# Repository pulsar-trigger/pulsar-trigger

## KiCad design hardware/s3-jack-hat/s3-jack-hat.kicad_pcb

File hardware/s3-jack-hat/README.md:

<!--
SPDX-License-Identifier: GPL-3.0-or-later
Copyright (C) 2026 Pulsar Trigger contributors
-->

# S3 Jack Hat (KiCad 10)

Source: written for Pulsar.

**Status: r0.1 built (JLC, 2026-11) and its header is mirrored end to end - it does not
work as shipped. Rework below; r0.2 = regenerate from the fixed
[tools/hat2.py](tools/hat2.py) with `tools/build.sh` before ordering again.** The files in
`out/` and the `.kicad_pcb` are still r0.1. The PJ-242 pin roles are read from the
maker's drawing, not yet measured.

## 🔴 r0.1: header mirrored end to end (found 2026-11-24)

Plugged in with its components towards the stick's back (the only way the case takes it),
r0.1's square pad 1 sits at the **G3 / 5V_IN** end of the socket, not the G5 / GND end:

| r0.1 net | Pad | Meant for | Lands on (normal) | Lands on (upside down) |
| --- | --- | --- | --- | --- |
| Shutter (R1, U1) | 1 | G5 | G3 | the stick's GND (can never fire) |
| Board GND | 2 | GND | **5V_IN** | G5 |
| Focus (R3, U2) | 5 | G6 | G44 (UART TX) | **G0** (boot strap) |

So nothing fires the normal way. Upside down, focus follows G5 and G0, and G0 is tied to
the focus net, which can boot the stick into download mode. Use it neither way unrepaired.

**Rework (three wires, three pins):**

1. Clip or pull the header pins of **pads 1, 2 and 5** so they no longer enter the socket.
   Pad 2 is the one that matters: left in, it shorts 5V_IN to ground once step 2 is done.
2. Wire, on the board: **pad 1 → pad 15** (lands on G5), **pad 2 → pad 16** (GND),
   **pad 5 → pad 11** (G6). Pads 11, 15 and 16 are unconnected on r0.1.
3. Before power, plugged in normally: board GND to the stick's USB-C shell **beeps**;
   board GND to 5V_IN does **not**; the jack sleeve to board GND stays **open**.
4. Dry run with a plug: focus closes ring-sleeve, shutter closes tip-sleeve.

**Cause:** `GND_CORNER`'s side. The row was right, the end was not; the stick's label
reading below still holds for which row, and `("lower", "right")` is what the footprint
needs. With that value `hat2.py` maps G5 → pad 15, GND → pad 16, G6 → pad 11 - exactly
where the rework puts them.

This is a small board that plugs into the M5StickS3's Hat2-Bus and drives a Canon 2.5 mm
remote jack:

- G5 drives the shutter and G6 drives focus.
- Each line goes through an LTV-817S optocoupler, so the camera stays isolated from the
  stick.
- The board has no battery, charger, USB or boost converter. The stick runs on its own
  battery, or on a power bank plugged into its USB-C.

The larger hat (USB host bridge and LiPo power) is parked. It is in
[docs/hardware-s3-hat.md](../../docs/hardware-s3-hat.md) and [../s3-hat/](../s3-hat/).

```mermaid
flowchart LR
    G5["Hat2 G5"] --> R1["R1 330R"] --> U1["U1 LTV-817S<br/>shutter"]
    G6["Hat2 G6"] --> R3["R3 330R"] --> U2["U2 LTV-817S<br/>focus"]
    G5 --> R2["R2 100k to GND"]
    G6 --> R4["R4 100k to GND"]
    U1 -- "collector" --> TIP["J2 tip (pin 6)"]
    U2 -- "collector" --> RING["J2 ring (pin 4)"]
    U1 -- "emitter" --> SLV["J2 sleeve (pins 2+3)<br/>camera ground, not board GND"]
    U2 -- "emitter" --> SLV
```

## 🔴 Unverified before ordering

1. ~~**Header orientation.**~~ **Settled 2026-11-10, WRONG END - fixed 2026-11-24 to
   `("lower", "right")`, see "r0.1: header mirrored" above.** It read: `GND_CORNER = ("lower", "left")`
   in [tools/hat2.py](tools/hat2.py). GND is in the row nearer the stick's back, at the
   LED end of the socket. Four sources agree: the stick's back sticker, whose label lines
   are laid out like the rows, and Bruce firmware's CC1101, SD card and NRF24 wiring
   diagrams for the StickS3. The first guess, `("upper", "left")`, was wrong: it would
   have swapped every pin pair and put the focus line on G0, the boot strap pin.
2. **PJ-242 pin roles.** The pins were read from the maker's drawing: 6 = tip, 4 = ring,
   2 + 3 = sleeve, 5/7 = switch contacts. See "PJ-242 pin roles" in the parked spec.
   Check them with a meter and a Canon plug.

## Hat2-Bus pin map (source checked)

Two sources give the same map:

- **M5Stack's StickS3 docs PDF, page 10, "Hat2-Bus".** It lists the LEFT column as pins 1, 3, … 15 and the
  RIGHT column as pins 2, 4, … 16.
- **The stick's schematic, page 4 (the BTB small board, CN2, "2×8 female, plastic height
  8.5, P = 2.54").** It numbers the same socket the other way: pins 1–8 down one row and
  16–9 back up the other. The pairs across the socket (GND/G5, EXT_5V/G4, BOOT/G6, G1/G7,
  G8/G43, BAT/G44, 3V3/G2, 5V_IN/G3) are identical, so the two numberings describe the
  same socket.

This board uses M5's odd/even numbers.

| Column | 1 | 2 | 3 | 4 | 5 | 6 | 7 | 8 |
| --- | --- | --- | --- | --- | --- | --- | --- | --- |
| Odd pin (1–15) | GND | EXT_5V | G0 (Boot) | G1 | G8 | BAT | 3V3_L2 | 5V_IN |
| Even pin (2–16) | G5 | G4 | G6 | G7 | G43 | G44 | G2 | G3 |

**G5 and G6 are free.** In the stick's schematic, EXT_GPIO5/6 run only from the ESP32-S3
(GPIO5/GPIO6, pins 10/11) through the board-to-board connectors to the Hat socket. They
have no other load, pull or function. G0 and G3 are boot-strapping pins and are left
unconnected. Every pin except GND, G5 and G6 carries a no-connect flag.

## Files

| Path | What |
| --- | --- |
| `s3-jack-hat.kicad_pro`, `.kicad_sch`, `.kicad_pcb` | The project. The board is saved with its zones filled |
| `s3-jack-hat.kicad_dru` | Custom rule: the camera side (jack nets) keeps ≥ 1 mm from everything else |
| `s3-jack-hat.kicad_sym`, `s3-jack-hat.pretty/` | The PJ-242 symbol and footprint (generated) |
| `tools/hat2.py` | **The one orientation choice** (`GND_CORNER`) and the Hat2 map |
| `tools/gen_schematic.py` | Writes the schematic. Its symbol engine is copied from `../s3-hat/tools/` |
| `tools/gen_pcb.py` | Writes the PJ-242 footprint and the board from the exported netlist |
| `tools/check_netlist.py` | Asserts every required connection, and every unconnected pin |
| `tools/jlc_files.py` | Writes the JLC BOM and CPL |
| `tools/build.sh` | Runs everything above, then exports the fabrication files |
| `out/` | ERC/DRC reports, netlist, Gerbers + drill (folder and zip), BOM, CPL, schematic PDF, renders |

**Edit the scripts, not the KiCad files.** The next build overwrites any hand edit.

## Regenerate and check

```sh
hardware/s3-jack-hat/tools/build.sh     # exit 0 = everything below passed
```

The script stops at the first failure. It runs:

1. the footprint;
2. the schematic;
3. ERC (`--exit-code-violations`, so any warning fails too);
4. the netlist export and `check_netlist.py`;
5. the board;
6. DRC with zone refill and schematic parity. It fails on any error, or on any warning
   other than the one expected below;
7. the Gerbers, drill files, position file, JLC CSVs, schematic PDF and renders.

**Results on 2026-11-10:**

- **ERC:** 0 violations.
- **Netlist check:** all 48 checks pass (exit 0). Verified that it can fail: a netlist
  with the sleeve merged into GND fails it (exit 1).
- **DRC:** 0 errors, 0 unconnected, 0 schematic-parity issues, and 1 warning. The warning
  is `lib_footprint_mismatch` on J1, because the generator drops the header's silkscreen
  where it would hang over the board edge.
- **The isolation rule fires.** A test GND via placed 0.6 mm from the tip pad was flagged:
  "rule 'camera side isolation' clearance 1.0000 mm; actual 0.6000 mm". The default
  0.2 mm rule would have passed it.

The 3D renders show only the bare board. This KiCad install has no 3D models, so no part
bodies are drawn.

## BOM (JLC parts checked 2026-11-10 through JLC's parts API)

| Ref | Part | LCSC | JLC type | Stock 11-10 | Notes |
| --- | --- | --- | --- | --- | --- |
| J1 | Hong Cheng HC-PZ254-13.8L-2x8PWA, 2×8 right-angle male, 2.54 mm | C27985210 | Extended | 1381 | Through-hole: needs JLC's THT assembly, or hand soldering. It was chosen over C54907672 because it has a drawing (2.5 mm insulator, 6.0 mm mating pin, 3.0 mm tail, Ø1.02 holes) |
| J2 | Shou Han PJ-242, 2.5 mm SMD jack | C431536 | Extended | 16411 | Footprint drawn from the maker's land pattern |
| U1, U2 | Lite-On LTV-817S-TA1-C | C109227 | Basic | 382366 | SMD-4 |
| R1, R3 | 330 Ω 0603 1 % (0603WAF3300T5E) | C23138 | Basic | 2735562 | ~5–6 mA LED current at 3.3 V |
| R2, R4 | 100 kΩ 0603 1 % (0603WAF1003T5E) | C25803 | Basic | 15778519 | Keep the LEDs off while the S3 boots |

**Alternate header: C54907672,** the Shou Han PZ2.54-2x8PWZ-L18.8-A (Extended, 748 in
stock). JLC lists the same attributes for it (2.5 mm insulator, 6 mm mating pin, 3 mm
tail), but there is no drawing. Its "L18.8" suffix is 5 mm longer than Hong Cheng's
"L13.8", so check its pin length before you substitute it.

**JLC rotation.** The CPL carries KiCad's rotations. JLC's library orientation differs
for some parts, most likely the SMDIP-4 and the PJ-242. Check every part in JLC's
placement preview before you pay.

## Mechanics: numbers for the case

**Board frame.** The stick lies screen up, with its Hat end touching the board.

- **u** runs across the board, west to east, as seen from above with the stick at the
  top of the view. u = 0 is the board's left edge.
- **v** runs away from the stick. v = 0 is the edge that touches the stick's end face.
- **Z** is height. Z = 0 is the board's top surface, which is level with the stick's back.

| Item | Value |
| --- | --- |
| Board | **24.0 × 21.4 mm**, 1.6 mm FR4, square corners, 2 layers. Z −1.6 to 0, so the case floor under the hat sits 1.6 mm below the stick's back |
| Header pin columns | 8 columns at u = 3.11 + 2.54·(k−1), so 3.11 to 20.89, centred on u = 12.0 (the socket is centred across the stick) |
| Header pads in the board | lower row (pads 2–16) at v = 4.04; upper row (pads 1–15) at v = 6.58 |
| Header plastic body | on the board, v = 0 to 2.54, u ≈ 1.84 to 22.16, Z 0 to ~5.1. Its front face is the board edge and butts against the stick's end face |
| Header mating pins | 6.0 mm beyond the board edge (v = 0 to −6.0), into the socket. The socket is 8.5 mm deep |
| Header pin row heights | nominally Z = 1.27 (lower row) and 3.81 (upper row). The stick's socket rows sit 1.27 and 3.81 above its back, so the nominal match is exact. 🔴 The drawing gives the row pitch (2.54 ± 0.2) but not the absolute height above the PCB, so measure a sample |
| Jack body | u = 15.9 to 20.9, v = 10.9 to 21.4, Z 0 to 3.2. The tabs make it 6.5 wide |
| Jack opening | on the far edge (v = 21.4), centred at **u = 18.4**, **Z = +1.6**. Plug hole Ø2.6. The nose is Ø4.0 and stands 1.5 mm proud of the far edge (v 21.4 to 22.9); its bottom dips to Z −0.4, so it must overhang the edge. Cut the case wall about Ø4.2 around it |
| Optocouplers | U1 centre (6.6, 13.0), U2 centre (6.6, 18.6). Body 6.5 × 4.6, ≤ 4.35 tall |
| Tallest part | the header body, ~5.1 mm (the socket opening is 5.1 tall) |
| Mounting holes | **None.** An M2 hole needs about a Ø4.9 keep-out, and no clear spot that size exists on 24 × 21.4. Hold the board on a ledge at its edges; the header in the stick and the jack nose in the wall locate it |
| Length beyond the stick | 21.4 mm of board, plus 1.5 mm of jack nose |

**Why the jack is on the far edge:** the cable leaves in line with the stick, away from
it, and does not block the stick's side buttons. The USB-C is on the stick's other end,
so the two cables leave from opposite ends. A side exit would put the 12 mm-long jack
across the 24 mm width, push the optocouplers elsewhere, and make the board longer.

**Isolation.** The GND pour covers only the stick side: the band along the header, and
the LED half of the optocouplers. The camera side carries no pour: the tip, ring and
sleeve tracks, the transistor half of each optocoupler, and the jack. A custom DRC rule
keeps ≥ 1 mm of copper clearance between the camera side and anything else, including
the Hat pins that carry the stick's rails.

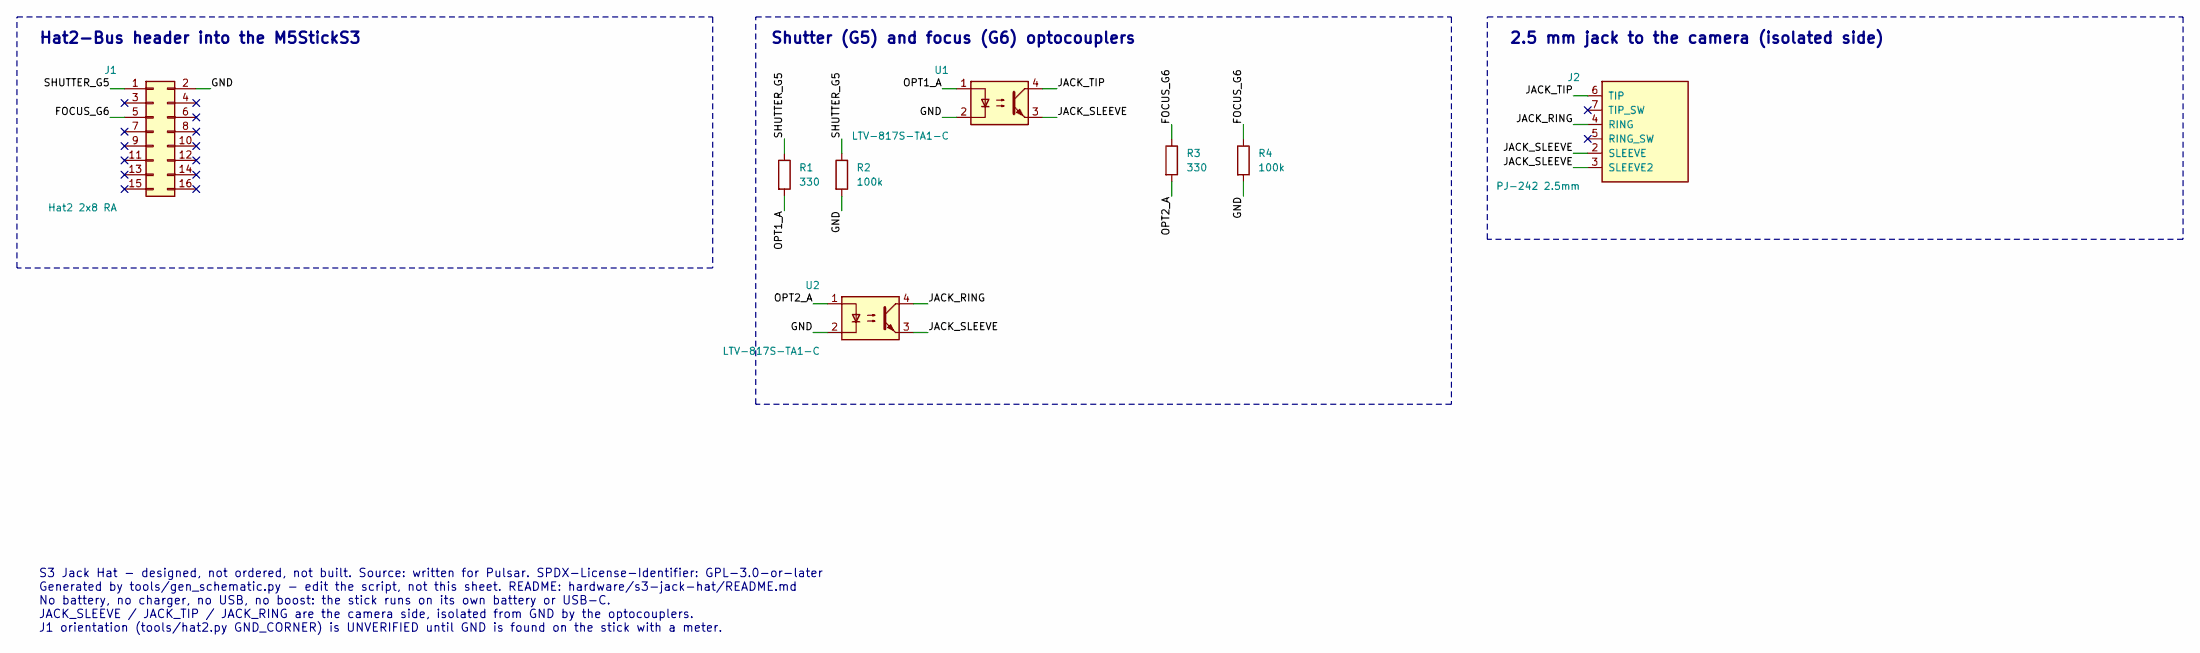
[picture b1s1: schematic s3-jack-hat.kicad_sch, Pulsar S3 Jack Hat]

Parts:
J1: Hat2 2x8 RA; PinHeader_2x08_P2.54mm_Horizontal; MPN HC-PZ254-13.8L-2x8PWA; LCSC C27985210
J2: PJ-242 2.5mm; PJ-242_ShouHan; MPN PJ-242; LCSC C431536
R1, R3: 330; R_0603_1608Metric; MPN 0603WAF3300T5E; LCSC C23138
R2, R4: 100k; R_0603_1608Metric; MPN 0603WAF1003T5E; LCSC C25803
U1, U2: LTV-817S-TA1-C; SMDIP-4_W9.53mm; MPN LTV-817S-TA1-C; LCSC C109227

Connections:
/FOCUS_G6: J1.5, R3.1, R4.1
/GND: J1.2, R2.2, R4.2, U1.2, U2.2
/JACK_RING: J2.4 (RING), U2.4
/JACK_SLEEVE: J2.2 (SLEEVE), J2.3 (SLEEVE2), U1.3, U2.3
/JACK_TIP: J2.6 (TIP), U1.4
/OPT1_A: R1.2, U1.1
/OPT2_A: R3.2, U2.1
/SHUTTER_G5: J1.1, R1.1, R2.1

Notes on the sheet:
Hat2-Bus header into the M5StickS3
Shutter (G5) and focus (G6) optocouplers
2.5 mm jack to the camera (isolated side)
S3 Jack Hat - designed, not ordered, not built. Source: written for Pulsar. SPDX-License-Identifier: GPL-3.0-or-later Generated by tools/gen_schematic.py - edit the script, not this sheet. README: hardware/s3-jack-hat/README.md No battery, no charger, no USB, no boost: the stick runs on its own bat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

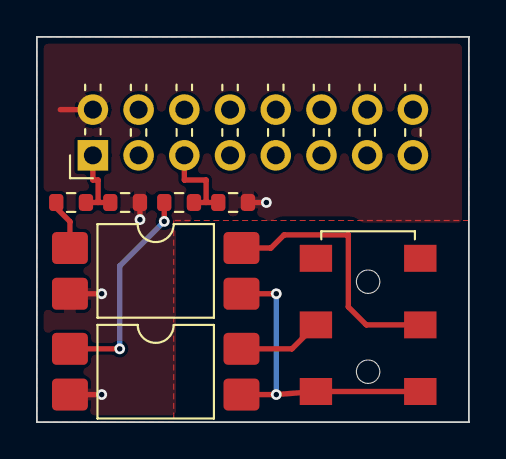
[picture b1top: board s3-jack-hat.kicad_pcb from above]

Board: 2 copper layers, 24.0 x 21.4 mm, 8 parts (0 on the bottom side), 8 nets.

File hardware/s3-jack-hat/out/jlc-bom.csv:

Comment,Designator,Footprint,LCSC
Hat2 2x8 RA,J1,PinHeader_2x08_P2.54mm_Horizontal,C27985210
PJ-242 2.5mm,J2,PJ-242_ShouHan,C431536
330,"R1,R3",R_0603_1608Metric,C23138
100k,"R2,R4",R_0603_1608Metric,C25803
LTV-817S-TA1-C,"U1,U2",SMDIP-4_W9.53mm,C109227

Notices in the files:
hardware/s3-jack-hat/s3-jack-hat.kicad_pcb:
Pulsar Trigger contributors - GPL-3.0-or-later
